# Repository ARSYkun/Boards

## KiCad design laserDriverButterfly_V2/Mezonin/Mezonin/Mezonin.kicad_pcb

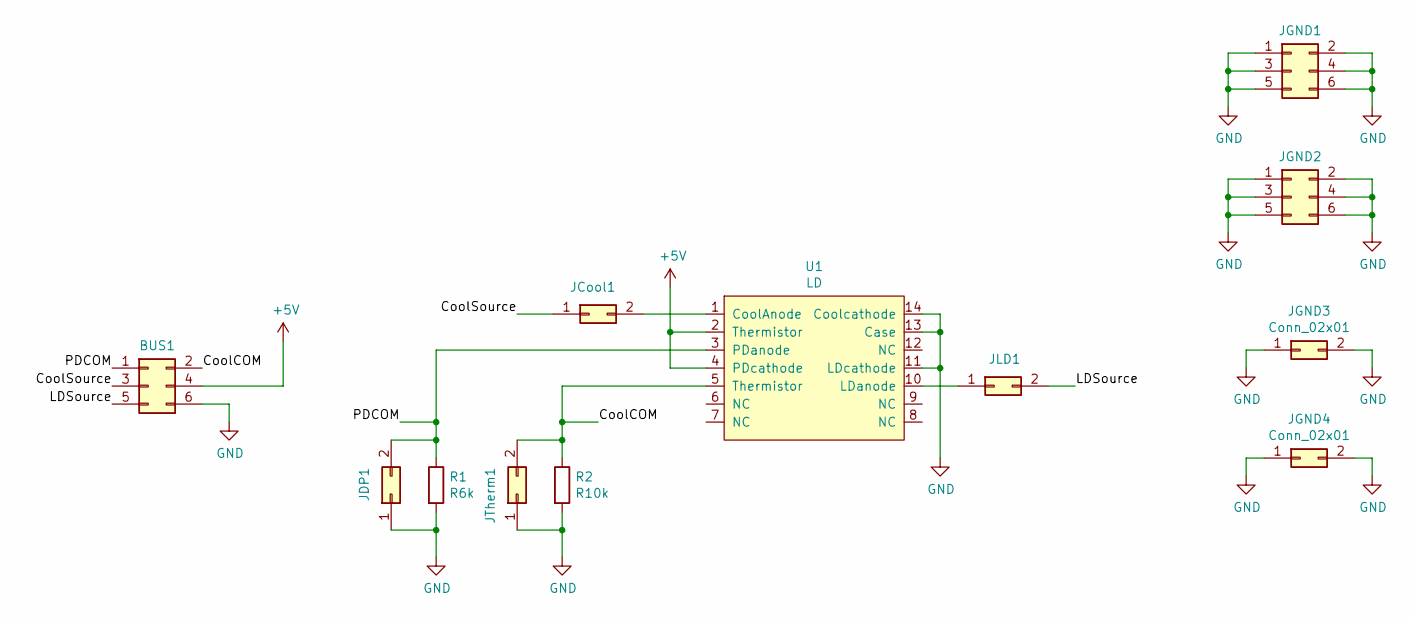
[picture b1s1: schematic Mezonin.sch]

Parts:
BUS1: Conn_02x03_Odd_Even; PinHeader_2x03_P2.54mm_Vertical
JCool1: Conn_02x01; PinHeader_1x02_P2.54mm_Vertical
JDP1: Conn_02x01; PinHeader_1x02_P2.54mm_Vertical
JGND1, JGND2: Conn_02x03_Odd_Even; PinHeader_2x03_P2.54mm_Vertical
JGND3, JGND4: Conn_02x01; PinHeader_1x02_P2.54mm_Vertical
JLD1: Conn_02x01; PinHeader_1x02_P2.54mm_Vertical
JTherm1: Conn_02x01; PinHeader_1x02_P2.54mm_Vertical
R1: R6k; R_1206_3216Metric_Pad1.42x1.75mm_HandSolder
R2: R10k; R_1206_3216Metric_Pad1.42x1.75mm_HandSolder
U1: LD; LD14BF

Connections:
+5V: BUS1.4, U1.2 (Thermistor), U1.4 (PDcathode)
/CoolCOM: BUS1.2, JTherm1.2, R2.1, U1.5 (Thermistor)
/CoolSource: BUS1.3, JCool1.1
/LDSource: BUS1.5, JLD1.2
/PDCOM: BUS1.1, JDP1.2, R1.1, U1.3 (PDanode)
GND: BUS1.6, JDP1.1, JGND1.1, JGND1.2, JGND1.3, JGND1.4, JGND1.5, JGND1.6, JGND2.1, JGND2.2, JGND2.3, JGND2.4, JGND2.5, JGND2.6, JGND3.1, JGND3.2, JGND4.1, JGND4.2, JTherm1.1, R1.2, R2.2, U1.11 (LDcathode), U1.13 (Case), U1.14 (Coolcathode)
unnamed: JCool1.2, U1.1 (CoolAnode)
unnamed: JLD1.1, U1.10 (LDanode)

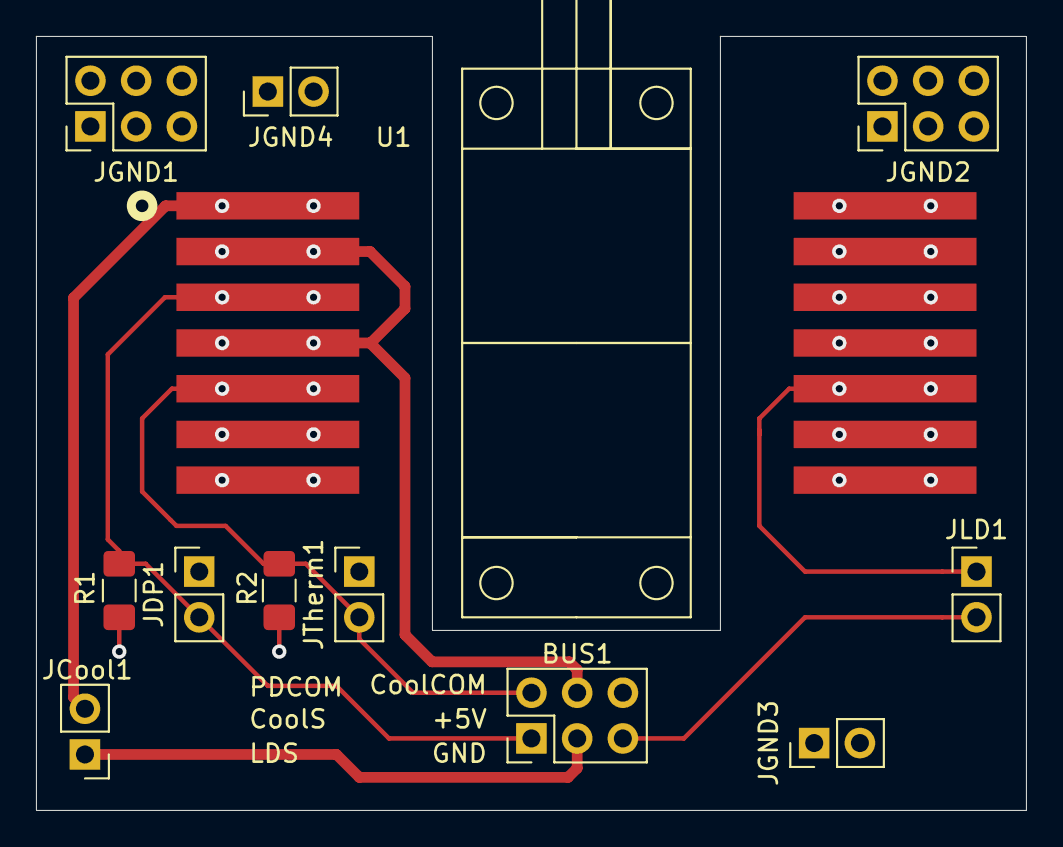
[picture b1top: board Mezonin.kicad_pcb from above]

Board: 2 copper layers, 55.0 x 43.0 mm, 12 parts (0 on the bottom side), 8 nets.

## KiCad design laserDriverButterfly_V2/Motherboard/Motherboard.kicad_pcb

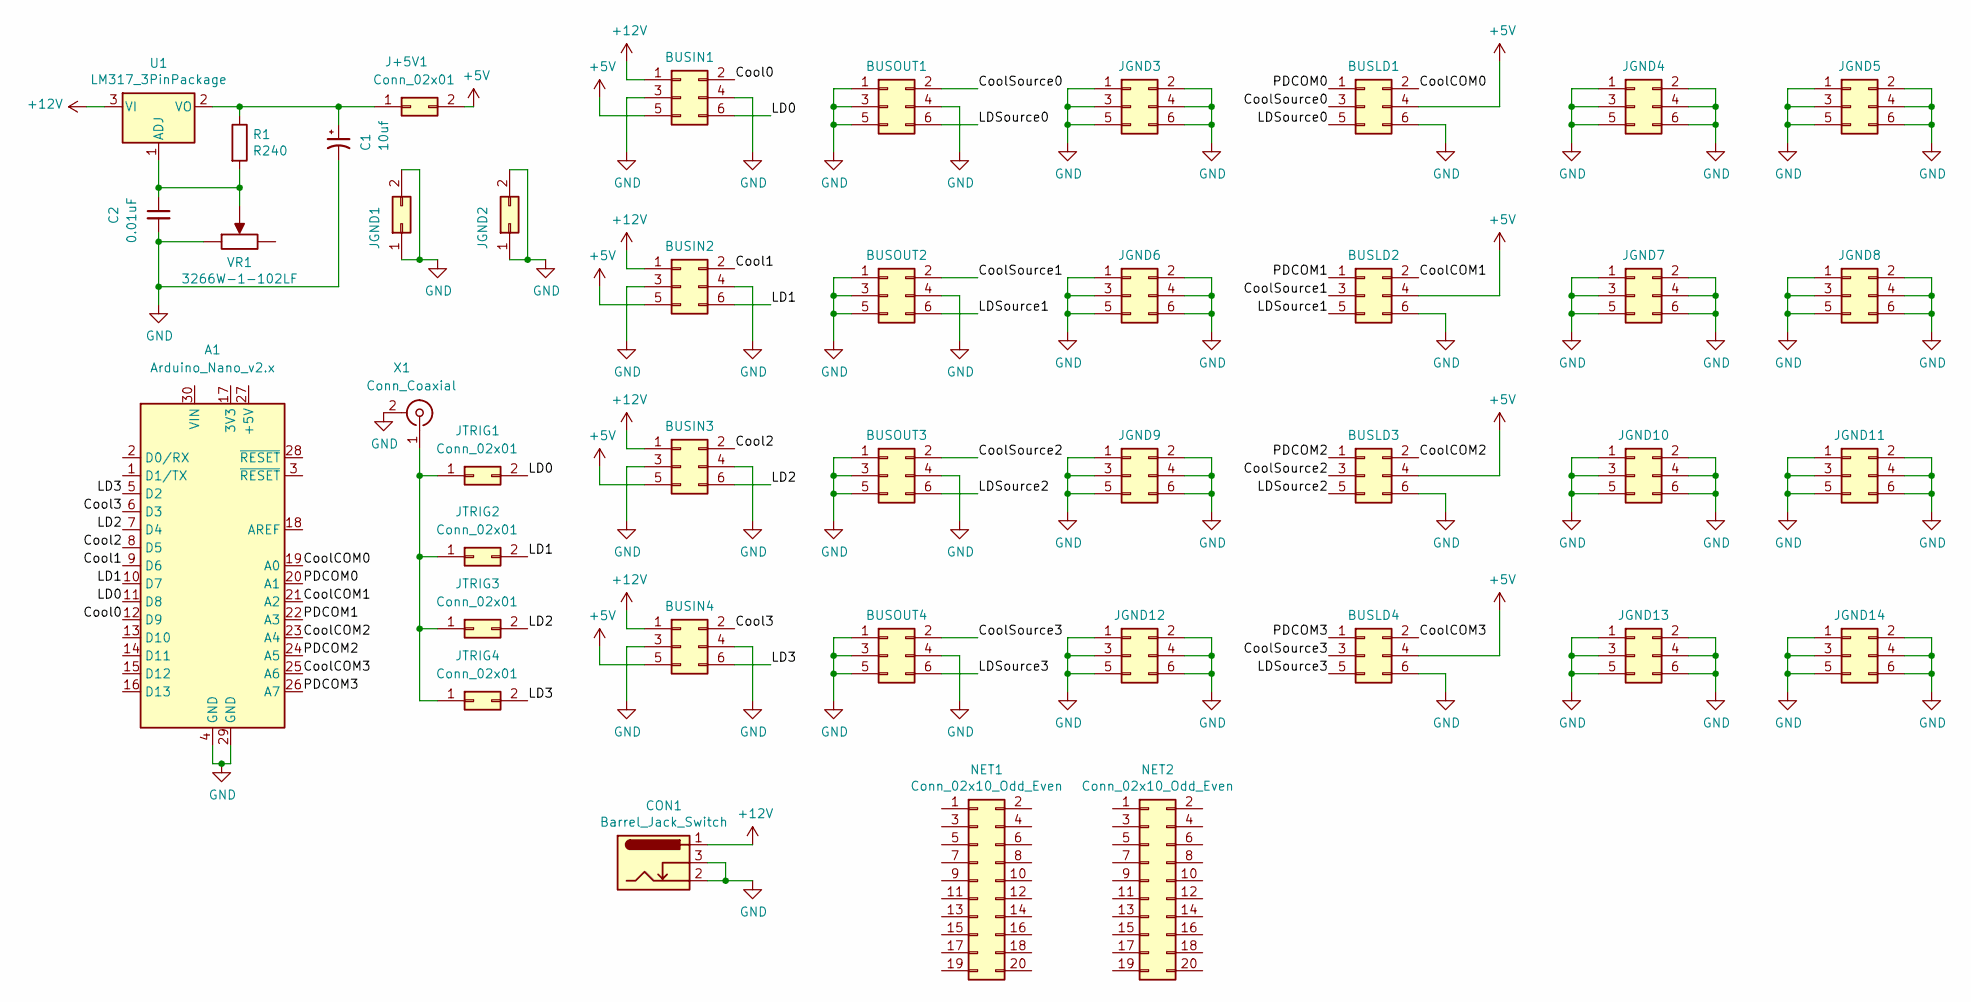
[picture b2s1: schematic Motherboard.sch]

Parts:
A1: Arduino_Nano_v2.x; Arduino_Nano
BUSIN1, BUSIN2, BUSIN3, BUSIN4: Conn_02x03_Odd_Even; PinHeader_2x03_P2.54mm_Vertical
BUSLD1, BUSLD2, BUSLD3, BUSLD4: Conn_02x03_Odd_Even; PinHeader_2x03_P2.54mm_Vertical
BUSOUT1, BUSOUT2, BUSOUT3, BUSOUT4: Conn_02x03_Odd_Even; PinHeader_2x03_P2.54mm_Vertical
C1: 10uf; C_1812_4532Metric
C2: 0.01uF; C_1812_4532Metric
CON1: Barrel_Jack_Switch; BarrelJack_Horizontal
J+5V1: Conn_02x01; PinHeader_2x01_P2.54mm_Vertical
JGND1, JGND2: Conn_02x01; PinHeader_2x01_P2.54mm_Vertical
JGND3, JGND4, JGND5, JGND6, JGND7, JGND8, JGND9, JGND10, JGND11, JGND12, JGND13, JGND14: Conn_02x03_Odd_Even; PinHeader_2x03_P2.54mm_Vertical
JTRIG1, JTRIG2, JTRIG3, JTRIG4: Conn_02x01; PinHeader_2x01_P2.54mm_Vertical
NET1, NET2: Conn_02x10_Odd_Even; PinHeader_2x10_P2.54mm_Vertical
R1: R240; R_1206_3216Metric_Pad1.42x1.75mm_HandSolder
U1: LM317_3PinPackage; TO-263-2
VR1: 3266W-1-102LF; Potentiometer_Bourns_3266W_Vertical
X1: Conn_Coaxial; SMA_Amphenol_132203-12_Horizontal

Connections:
+5V: BUSIN1.5, BUSIN2.5, BUSIN3.5, BUSIN4.5, BUSLD1.4, BUSLD2.4, BUSLD3.4, BUSLD4.4, J+5V1.2
+12V: BUSIN1.1, BUSIN2.1, BUSIN3.1, BUSIN4.1, CON1.1, U1.3 (VI)
/Cool0: A1.12 (D9), BUSIN1.2
/Cool1: A1.9 (D6), BUSIN2.2
/Cool2: A1.8 (D5), BUSIN3.2
/Cool3: A1.6 (D3), BUSIN4.2
/CoolCOM0: A1.19 (A0), BUSLD1.2
/CoolCOM1: A1.21 (A2), BUSLD2.2
/CoolCOM2: A1.23 (A4), BUSLD3.2
/CoolCOM3: A1.25 (A6), BUSLD4.2
/CoolSource0: BUSLD1.3, BUSOUT1.2
/CoolSource1: BUSLD2.3, BUSOUT2.2
/CoolSource2: BUSLD3.3, BUSOUT3.2
/CoolSource3: BUSLD4.3, BUSOUT4.2
/LD0: A1.11 (D8), BUSIN1.6, JTRIG1.2
/LD1: A1.10 (D7), BUSIN2.6, JTRIG2.2
/LD2: A1.7 (D4), BUSIN3.6, JTRIG3.2
/LD3: A1.5 (D2), BUSIN4.6, JTRIG4.2
/LDSource0: BUSLD1.5, BUSOUT1.6
/LDSource1: BUSLD2.5, BUSOUT2.6
/LDSource2: BUSLD3.5, BUSOUT3.6
/LDSource3: BUSLD4.5, BUSOUT4.6
/PDCOM0: A1.20 (A1), BUSLD1.1
/PDCOM1: A1.22 (A3), BUSLD2.1
/PDCOM2: A1.24 (A5), BUSLD3.1
/PDCOM3: A1.26 (A7), BUSLD4.1
GND: A1.4 (GND), A1.29 (GND), BUSIN1.3, BUSIN1.4, BUSIN2.3, BUSIN2.4, BUSIN3.3, BUSIN3.4, BUSIN4.3, BUSIN4.4, BUSLD1.6, BUSLD2.6, BUSLD3.6, BUSLD4.6, BUSOUT1.1, BUSOUT1.3, BUSOUT1.4, BUSOUT1.5, BUSOUT2.1, BUSOUT2.3, BUSOUT2.4, BUSOUT2.5, BUSOUT3.1, BUSOUT3.3, BUSOUT3.4, BUSOUT3.5, BUSOUT4.1, BUSOUT4.3, BUSOUT4.4, BUSOUT4.5, C1.2, C2.2, CON1.2, CON1.3, JGND1.1, JGND1.2, JGND2.1, JGND2.2, JGND3.1, JGND3.2, JGND3.3, JGND3.4, JGND3.5, JGND3.6, JGND4.1, JGND4.2, JGND4.3, JGND4.4, JGND4.5, JGND4.6, JGND5.1, JGND5.2, JGND5.3, JGND5.4, JGND5.5, JGND5.6, JGND6.1, JGND6.2, JGND6.3, JGND6.4, JGND6.5, JGND6.6, JGND7.1, JGND7.2, JGND7.3, JGND7.4, JGND7.5, JGND7.6, JGND8.1, JGND8.2, JGND8.3, JGND8.4, JGND8.5, JGND8.6, JGND9.1, JGND9.2, JGND9.3, JGND9.4, JGND9.5, JGND9.6, JGND10.1, JGND10.2, JGND10.3, JGND10.4, JGND10.5, JGND10.6, JGND11.1, JGND11.2, JGND11.3, JGND11.4, JGND11.5, JGND11.6, JGND12.1, JGND12.2, JGND12.3, JGND12.4, JGND12.5, JGND12.6, JGND13.1, JGND13.2, JGND13.3, JGND13.4, JGND13.5, JGND13.6, JGND14.1, JGND14.2, JGND14.3, JGND14.4, JGND14.5, JGND14.6, VR1.1, X1.2 (Ext)
unnamed: C1.1, J+5V1.1, R1.1, U1.2 (VO)
unnamed: C2.1, R1.2, U1.1 (ADJ), VR1.2
unnamed: JTRIG1.1, JTRIG2.1, JTRIG3.1, JTRIG4.1, X1.1 (In)

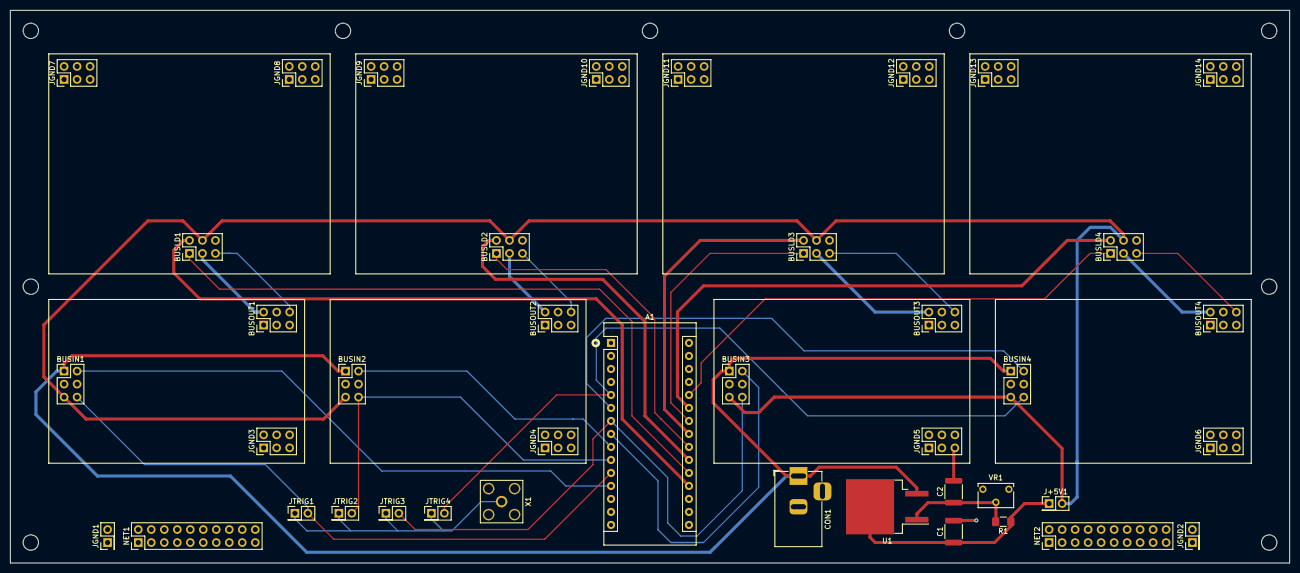
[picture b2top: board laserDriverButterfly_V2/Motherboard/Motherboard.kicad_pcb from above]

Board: 2 copper layers, 250.0 x 108.0 mm, 41 parts (0 on the bottom side), 30 nets.

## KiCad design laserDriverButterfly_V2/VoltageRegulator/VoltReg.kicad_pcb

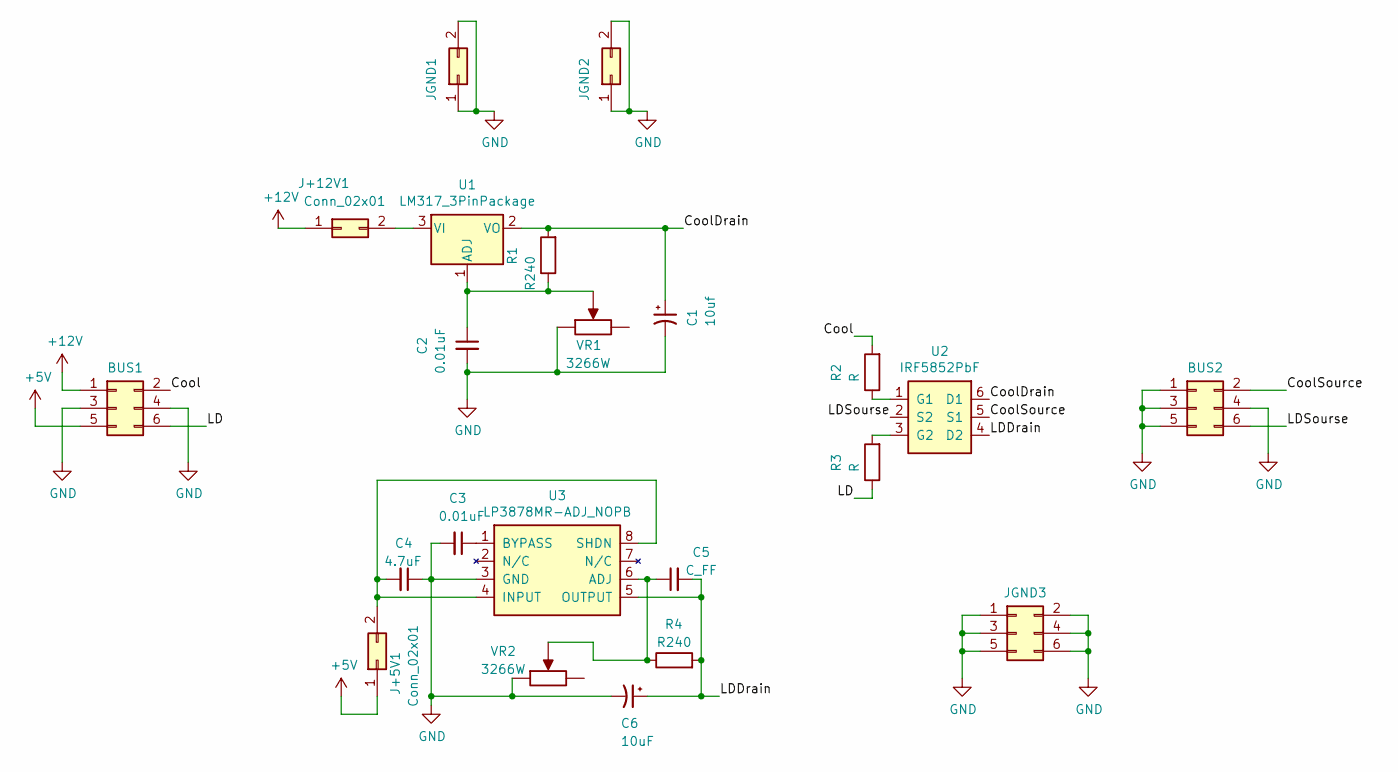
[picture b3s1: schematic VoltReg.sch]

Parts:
BUS1, BUS2: Conn_02x03_Odd_Even; PinHeader_2x03_P2.54mm_Vertical
C1: 10uf; C_1812_4532Metric
C2, C3: 0.01uF; C_1812_4532Metric
C4: 4.7uF; C_1812_4532Metric
C5: C_FF; C_1812_4532Metric
C6: 10uF; C_1812_4532Metric
J+5V1, J+12V1: Conn_02x01; PinHeader_2x01_P2.54mm_Vertical
JGND1, JGND2: Conn_02x01; PinHeader_2x01_P2.54mm_Vertical
JGND3: Conn_02x03_Odd_Even; PinHeader_2x03_P2.54mm_Vertical
R1, R4: R240; R_1206_3216Metric_Pad1.42x1.75mm_HandSolder
R2, R3: R; R_1206_3216Metric_Pad1.42x1.75mm_HandSolder
U1: LM317_3PinPackage; TO-263-2
U2: IRF5852PbF; TSOP-6_1.65x3.05mm_P0.95mm
U3: LP3878MR-ADJ_NOPB; HSOP-8-1EP_3.9x4.9mm_P1.27mm_EP2.41x3.1mm
VR1, VR2: 3266W; Potentiometer_Bourns_3266W_Vertical

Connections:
+5V: BUS1.5, J+5V1.1
+12V: BUS1.1, J+12V1.1
/Cool: BUS1.2, R2.2
/CoolDrain: C1.1, R1.2, U1.2 (VO), U2.6 (D1)
/CoolSource: BUS2.2, U2.5 (S1)
/LD: BUS1.6, R3.1
/LDDrain: C5.2, C6.1, R4.2, U2.4 (D2), U3.5 (OUTPUT)
/LDSourse: BUS2.6, U2.2 (S2)
GND: BUS1.3, BUS1.4, BUS2.1, BUS2.3, BUS2.4, BUS2.5, C1.2, C2.2, C3.2, C4.1, C6.2, JGND1.1, JGND1.2, JGND2.1, JGND2.2, JGND3.1, JGND3.2, JGND3.3, JGND3.4, JGND3.5, JGND3.6, U3.3 (GND), U3.9, VR1.1, VR2.1
unnamed: C2.1, R1.1, U1.1 (ADJ), VR1.2
unnamed: C3.1, U3.1 (BYPASS)
unnamed: C4.2, J+5V1.2, U3.4 (INPUT), U3.8 (SHDN)
unnamed: C5.1, R4.1, U3.6 (ADJ), VR2.2
unnamed: J+12V1.2, U1.3 (VI)
unnamed: R2.1, U2.1 (G1)
unnamed: R3.2, U2.3 (G2)

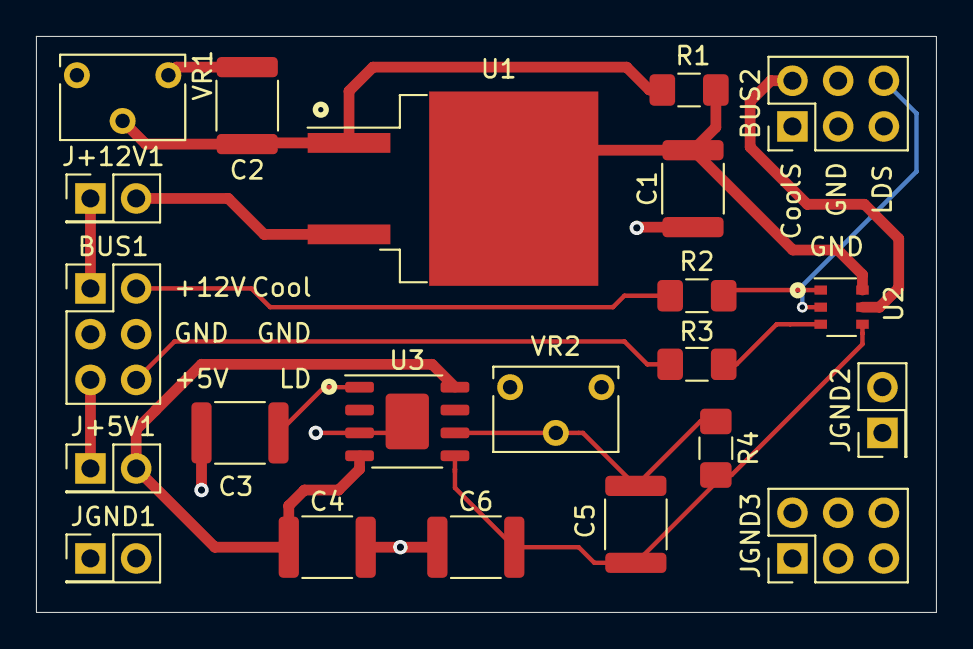
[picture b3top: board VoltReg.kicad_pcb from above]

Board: 2 copper layers, 50.0 x 32.0 mm, 22 parts (0 on the bottom side), 16 nets.

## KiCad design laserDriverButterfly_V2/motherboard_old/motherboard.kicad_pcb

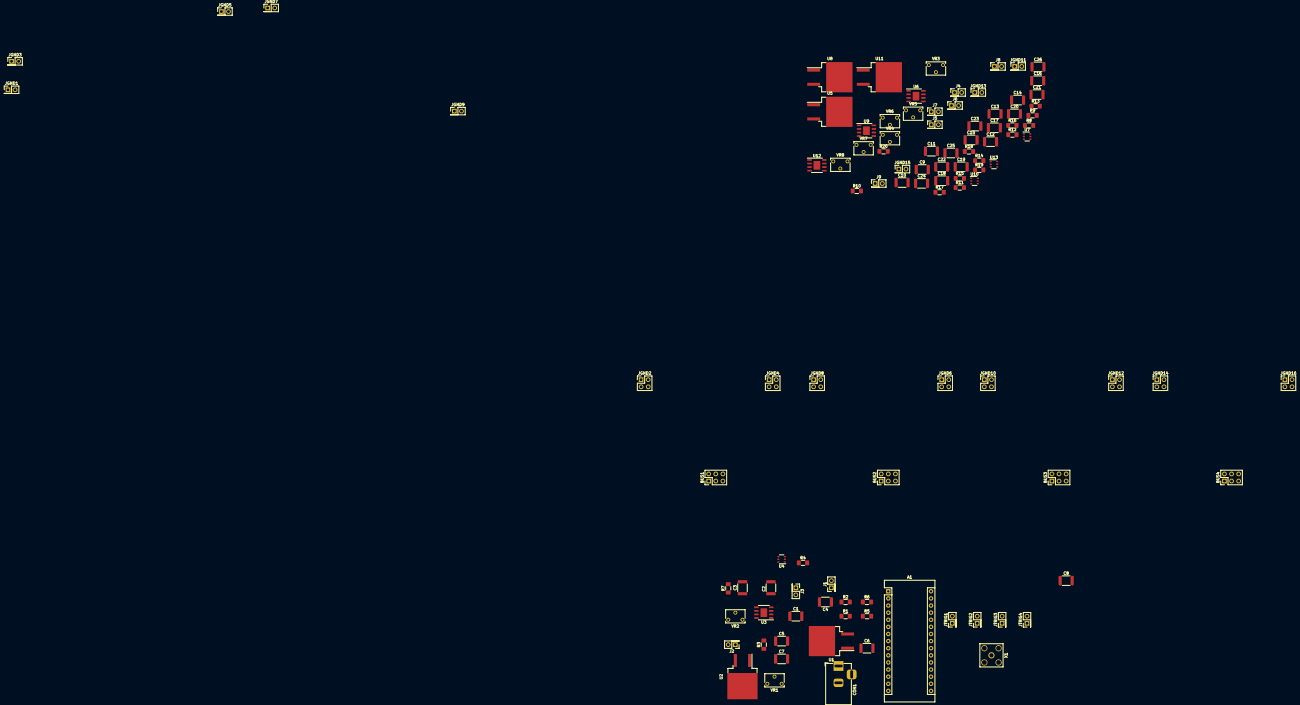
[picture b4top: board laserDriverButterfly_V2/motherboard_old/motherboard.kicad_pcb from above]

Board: 2 copper layers, 103 parts (0 on the bottom side), 63 nets, no tracks yet.

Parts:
A1: Arduino_Nano_v2.x; Arduino_Nano
BUS1, BUS2, BUS3, BUS4: Conn_02x03_Odd_Even; PinHeader_2x03_P2.54mm_Vertical
C1, C6, C7, C9, C13, C15, C19, C21, C25: 0.01uF; C_1812_4532Metric
C2, C10, C16, C22: 4.7uF; C_1812_4532Metric
C3, C11, C17, C23: C_FF; C_1812_4532Metric
C4, C5, C12, C18, C24: 10uf; C_1812_4532Metric
C8, C14, C20, C26: 10uF; C_1812_4532Metric
CON1: Barrel_Jack_Switch; BarrelJack_Horizontal
J1, J2, J3, J4, J5, J6, J7, J8, J9: Conn_02x01; PinHeader_2x01_P2.54mm_Vertical
JGND1, JGND3, JGND5, JGND7, JGND9, JGND11, JGND13, JGND15: Conn_02x01; PinHeader_2x01_P2.54mm_Vertical
JGND2, JGND4, JGND6, JGND8, JGND10, JGND12, JGND14, JGND16: Conn_02x02_Odd_Even; PinHeader_2x02_P2.54mm_Vertical
JTRIG1, JTRIG2, JTRIG3, JTRIG4: Conn_02x01; PinHeader_2x01_P2.54mm_Vertical
R1, R3, R7, R9, R11, R13, R15, R17, R19: R240; R_1206_3216Metric_Pad1.42x1.75mm_HandSolder
R2, R4, R6, R8, R10, R12, R14, R16, R18, R20: R; R_1206_3216Metric_Pad1.42x1.75mm_HandSolder
R5: R720; R_1206_3216Metric_Pad1.42x1.75mm_HandSolder
U1, U2, U5, U8, U11: LM317_3PinPackage; TO-263-2
U3, U6, U9, U12: LP3878MR-ADJ_NOPB; HSOP-8-1EP_3.9x4.9mm_P1.27mm_EP2.41x3.1mm
U4, U7, U10, U13: IRF5852PbF; TSOP-6_1.65x3.05mm_P0.95mm
VR1, VR2, VR3, VR4, VR5, VR6, VR7, VR8: 3266W; Potentiometer_Bourns_3266W_Vertical
X1: Conn_Coaxial; SMA_Amphenol_132203-12_Horizontal

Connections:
+5V: BUS1.4, BUS2.4, BUS3.4, BUS4.4, J1.2, J3.1, J5.1, J7.1, J9.1
+12V: CON1.1, J2.1, J4.1, J6.1, J8.1, U1.3
/Cool0: A1.6, R4.2
/Cool1: A1.8, R10.2
/Cool2: A1.9, R14.2
/Cool3: A1.12, R18.2
/CoolCOM0: A1.19, BUS1.2
/CoolCOM1: A1.21, BUS2.2
/CoolCOM2: A1.23, BUS3.2
/CoolCOM3: A1.25, BUS4.2
/CoolDrain0: C5.1, R3.2, U2.2, U4.6
/CoolDrain1: C12.1, R9.2, U5.2, U7.6
/CoolDrain2: C18.1, R13.2, U8.2, U10.6
/CoolDrain3: C24.1, R17.2, U11.2, U13.6
/CoolSource0: BUS1.3, U4.5
/CoolSource1: BUS2.3, U7.5
/CoolSource2: BUS3.3, U10.5
/CoolSource3: BUS4.3, U13.5
/LD0: A1.5, JTRIG1.2, R8.1
/LD1: A1.7, R12.1
/LD2: A1.10, JTRIG3.2, R16.1
/LD3: A1.11, JTRIG4.2, R20.1
/LDDrain0: C3.2, C8.1, R7.2, U3.5, U4.4
/LDDrain1: C11.2, C14.1, R11.2, U6.5, U7.4
/LDDrain2: C17.2, C20.1, R15.2, U9.5, U10.4
/LDDrain3: C23.2, C26.1, R19.2, U12.5, U13.4
/LDSourse0: BUS1.5, U4.2
/PDCOM0: A1.20, BUS1.1
/PDCOM1: A1.22, BUS2.1
/PDCOM2: A1.24, BUS3.1
/PDCOM3: A1.26, BUS4.1
GND: A1.4, A1.29, BUS1.6, BUS2.6, BUS3.6, BUS4.6, C1.2, C2.1, C4.2, C5.2, C6.2, C7.2, C8.2, C9.2, C10.1, C12.2, C13.2, C14.2, C15.2, C16.1, C18.2, C19.2, C20.2, C21.2, C22.1, C24.2, C25.2, C26.2, CON1.2, CON1.3, JGND1.1, JGND1.2, JGND2.1, JGND2.2, JGND2.3, JGND2.4, JGND3.1, JGND3.2, JGND4.1, JGND4.2, JGND4.3, JGND4.4, JGND5.1, JGND5.2, JGND6.1, JGND6.2, JGND6.3, JGND6.4, JGND7.1, JGND7.2, JGND8.1, JGND8.2, JGND8.3, JGND8.4, JGND9.1, JGND9.2, JGND10.1, JGND10.2, JGND10.3, JGND10.4, JGND11.1, JGND11.2, JGND12.1, JGND12.2, JGND12.3, JGND12.4, JGND13.1, JGND13.2, JGND14.1, JGND14.2, JGND14.3, JGND14.4, JGND15.1, JGND15.2, JGND16.1, JGND16.2, JGND16.3, JGND16.4, R5.2, R6.2, U3.3, U6.3, U9.3, U12.3, VR1.1, VR2.1, VR3.1, VR4.1, VR5.1, VR6.1, VR7.1, VR8.1, X1.2
unnamed: C1.1, U3.1
unnamed: C2.2, J3.2, U3.4, U3.8
unnamed: C3.1, R7.1, U3.6, VR2.2
unnamed: C4.1, J1.1, R1.1, R2.1, U1.2
unnamed: C6.1, R1.2, R2.2, R5.1, R6.1, U1.1
unnamed: C7.1, R3.1, U2.1, VR1.2
unnamed: C9.1, U6.1
unnamed: C10.2, J5.2, U6.4, U6.8
unnamed: C11.1, R11.1, U6.6, VR4.2
unnamed: C13.1, R9.1, U5.1, VR3.2
unnamed: C15.1, U9.1
unnamed: C16.2, J7.2, U9.4, U9.8
unnamed: C17.1, R15.1, U9.6, VR6.2
unnamed: C19.1, R13.1, U8.1, VR5.2
unnamed: C21.1, U12.1
unnamed: C22.2, J9.2, U12.4, U12.8
unnamed: C23.1, R19.1, U12.6, VR8.2
unnamed: C25.1, R17.1, U11.1, VR7.2
unnamed: J2.2, U2.3
unnamed: J4.2, U5.3
unnamed: J6.2, U8.3
unnamed: J8.2, U11.3
unnamed: JTRIG1.1, JTRIG2.1, JTRIG3.1, JTRIG4.1, X1.1
unnamed: R4.1, U4.1
unnamed: R8.2, U4.3
unnamed: R10.1, U7.1
unnamed: R12.2, U7.3
unnamed: R14.1, U10.1
unnamed: R16.2, U10.3
unnamed: R18.1, U13.1
unnamed: R20.2, U13.3

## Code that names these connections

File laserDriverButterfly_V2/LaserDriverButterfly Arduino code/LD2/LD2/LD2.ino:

#include <Wire.h>



  int PWMcoef = 255;
  int COM1 = 0;
  int COM2 = 0;

  // Для лазера 0
  int Cool0 = 9;
  int LD0 = 8;
  int CoolCOM0 = A0;
  int PDCOM0 = A1;

  // Для лазера 1
  int Cool1 = 6;
  int LD1 = 7;
  int CoolCOM1 = A2;
  int PDCOM1 = A3;

  // Для лазера 2
  int Cool2 = 5;
  int LD2 = 4;
  int CoolCOM2 = A4;
  int PDCOM2 = A5;

  // Для лазера 3
  int Cool3 = 3;
  int LD3 = 2;
  int CoolCOM3 = A6;
  int PDCOM3 = A7;


// Открытие IRF для включения лазера
void openIRF(int LD, int Cool, int PWMcoef) {  
    analogWrite(Cool, PWMcoef);
    delay(10);
    digitalWrite(LD, HIGH);
}

// Закрытие IRF для выключения лазера
void closeIRF(int LD, int Cool) {
  digitalWrite(LD, LOW);
  delay(10);
  digitalWrite(Cool, LOW);

}

// Считать токи фотодиода и кулера 
void readLaser(String num, int PDCOM, int CoolCOM) {

  Serial.print("PDCOM" + num + " = ");
  Serial.print(PDCOM);
  Serial.print("\t");

  Serial.print("CoolCOM" + num + " = ");
  Serial.print(CoolCOM);
  Serial.print("\n"); 


  
//  Serial.print("PDCOM0 = ");
//  Serial.print(analogRead(PDCOM0));
//  Serial.print("\t");
//
//  Serial.print("PDCOM1 = ");
//  Serial.print(analogRead(PDCOM1));
//  Serial.print("\t");
//
//  Serial.print("PDCOM2 = ");
//  Serial.print(analogRead(PDCOM2));
//  Serial.print("\t");
//
//  Serial.print("PDCOM3 = ");
//  Serial.println(analogRead(PDCOM3));
//
//
//  Serial.print("CoolCOM0 = ");
//  Serial.print(analogRead(CoolCOM0));
//  Serial.print("\t");
//
//  Serial.print("CoolCOM1 = ");
//  Serial.print(analogRead(CoolCOM1));
//  Serial.print("\t");
//
//  Serial.print("CoolCOM2 = ");
//  Serial.print(analogRead(CoolCOM2));
//  Serial.print("\t");
//
//  Serial.print("CoolCOM3 = ");
//  Serial.print(analogRead(CoolCOM3));
//  Serial.println("\n");

}

void setup() {
  Serial.begin(115200);
}

void loop() {

//  digitalWrite(LD0, HIGH);
//  delay(1);
//  digitalWrite(LD0, LOW);
//  delay(1);

 

  
  openIRF(LD0, Cool0, PWMcoef);  
  delay(10);
  COM1 = analogRead(PDCOM0);
  COM2 = analogRead(CoolCOM0);
  closeIRF(LD0, Cool0);
  readLaser("0", COM1, COM2);
  

  delay(10);
  
  openIRF(LD1, Cool1, PWMcoef);  
  delay(10);
  COM1 = analogRead(PDCOM1);
  COM2 = analogRead(CoolCOM1);
  closeIRF(LD1, Cool1);
  readLaser("1", COM1, COM2);
  
  delay(10);
  
  openIRF(LD2, Cool2, PWMcoef);  
  delay(10);
  COM1 = analogRead(PDCOM2);
  COM2 = analogRead(CoolCOM2);
  closeIRF(LD2, Cool2);
  readLaser("2", COM1, COM2);
  
  Serial.print("\n");
  delay(100);



  
}

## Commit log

2021-11-26 add boards with gerbers
2021-11-26 update mez
2021-11-26 update voltreg and motherboard
2021-11-26 Add receipt
2021-11-26 Add PDF
2022-03-14 Add LaserDriver board
2022-03-14 Add LaserDriver arduino
2022-03-14 Add PIN photodiode
2022-03-14 Add Chiller
2022-03-25 Add EV76C661 board
2022-03-25 Add EV76C661 datasheet
2022-03-25 Add Arduino code
2022-09-08 Add MAX3738ETG+
2022-09-08 Add SLD-1550-ANR
2022-09-08 Add TFD-50RA
2023-07-09 add XLIN1.7-2048SQ TE0
2023-07-09 add VRef_MEZ
2023-07-09 add XLIN1.7-2048 TE0
2024-02-22 add IPD171
2025-01-20 add Photomodule
2025-01-20 add AD Library
2025-01-24 add PDF Schematic
